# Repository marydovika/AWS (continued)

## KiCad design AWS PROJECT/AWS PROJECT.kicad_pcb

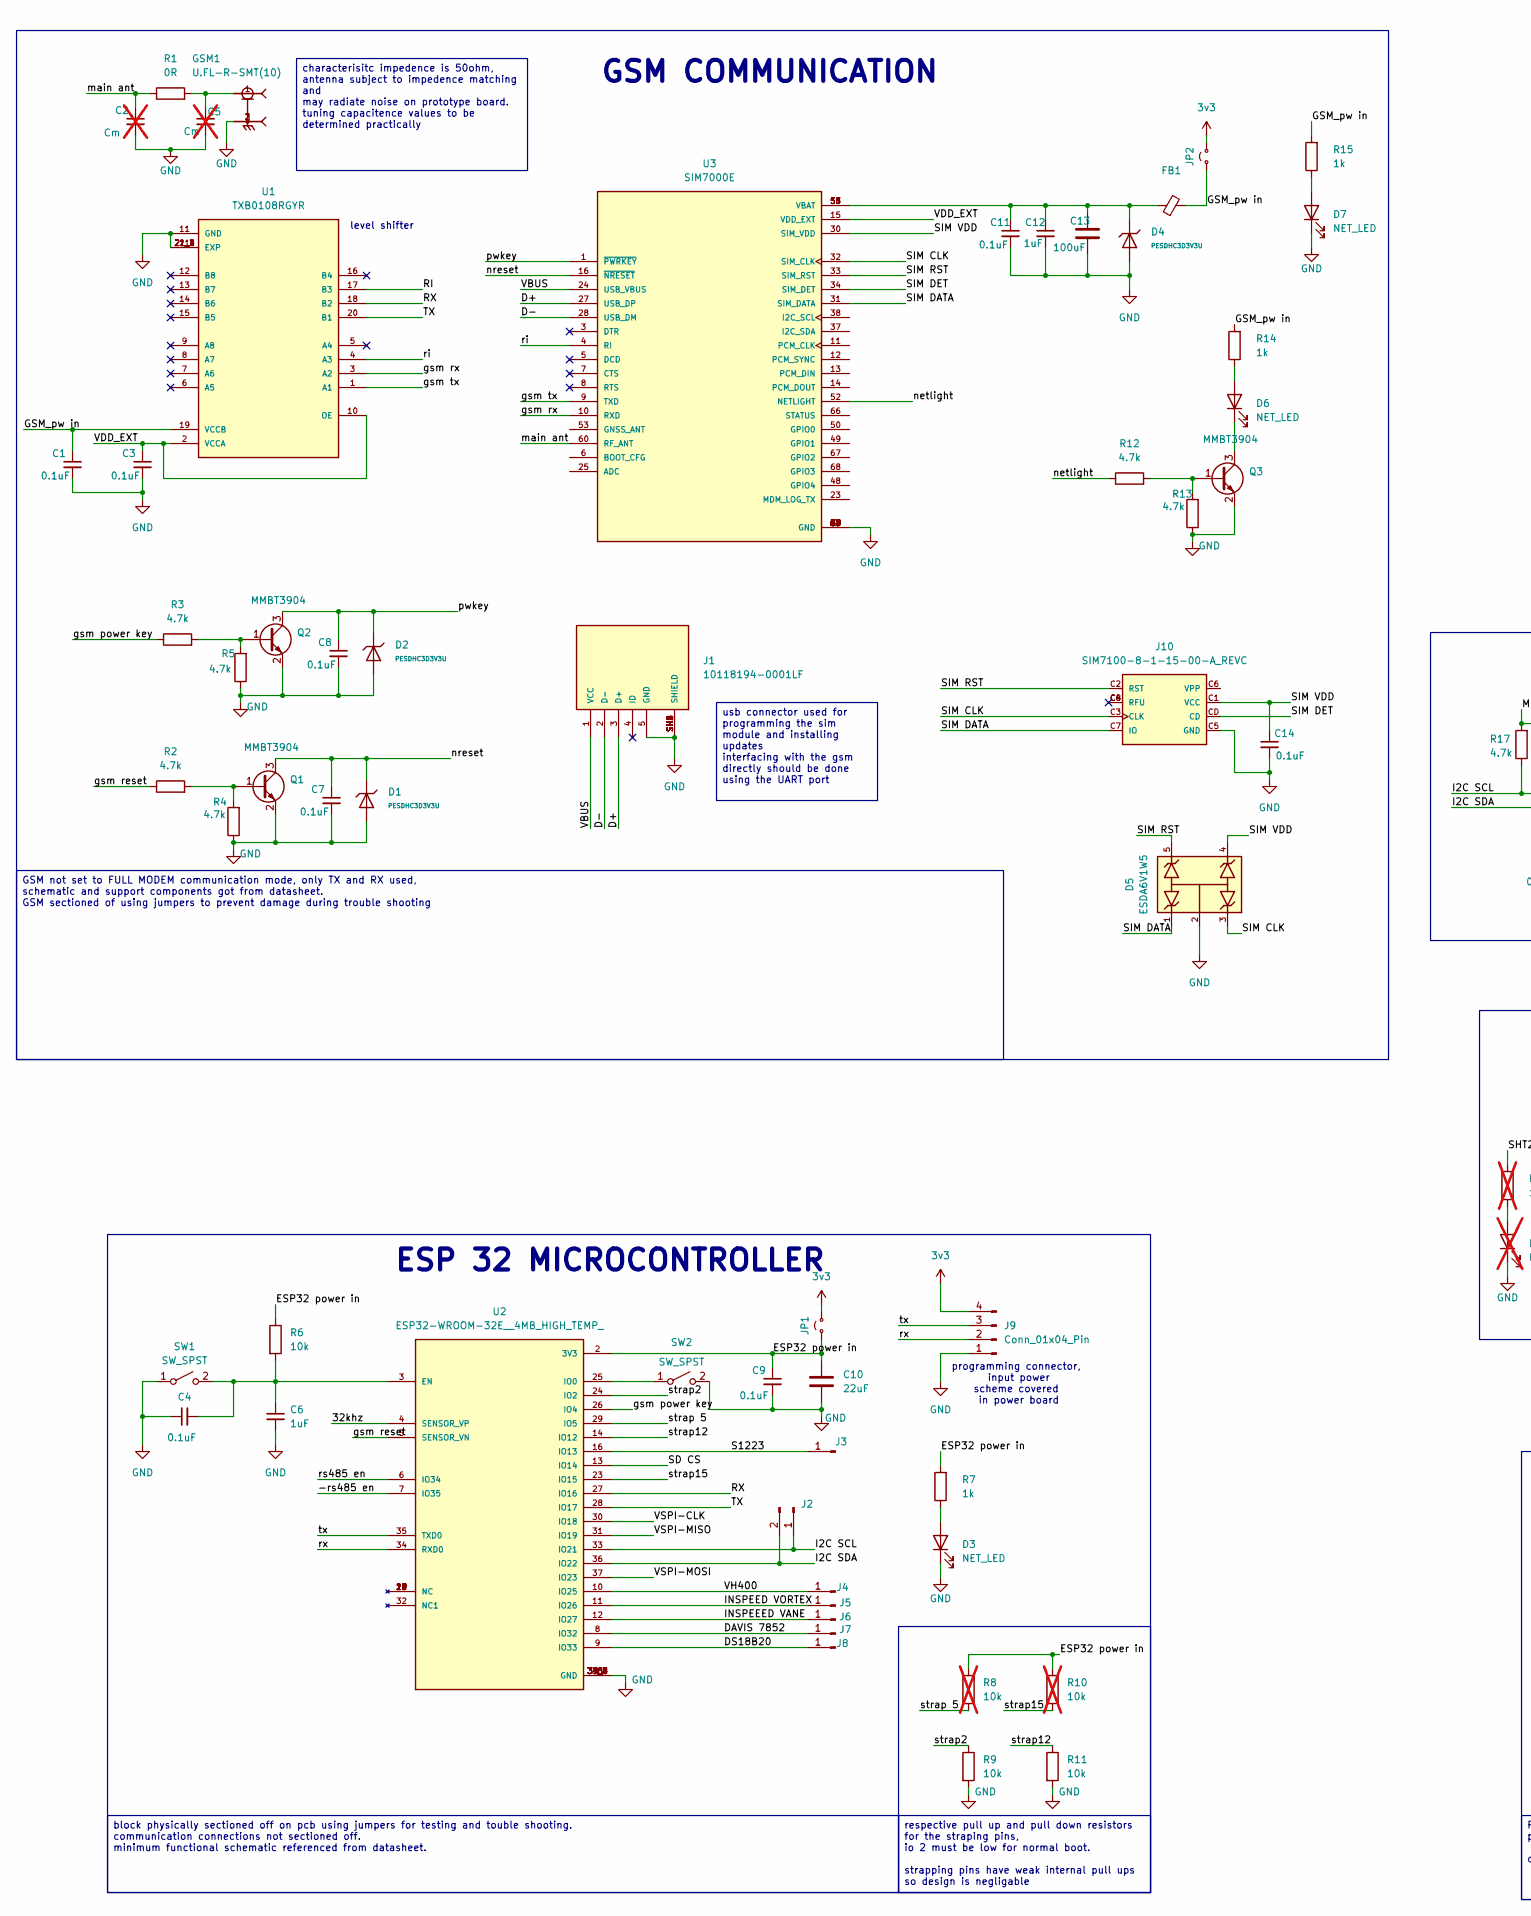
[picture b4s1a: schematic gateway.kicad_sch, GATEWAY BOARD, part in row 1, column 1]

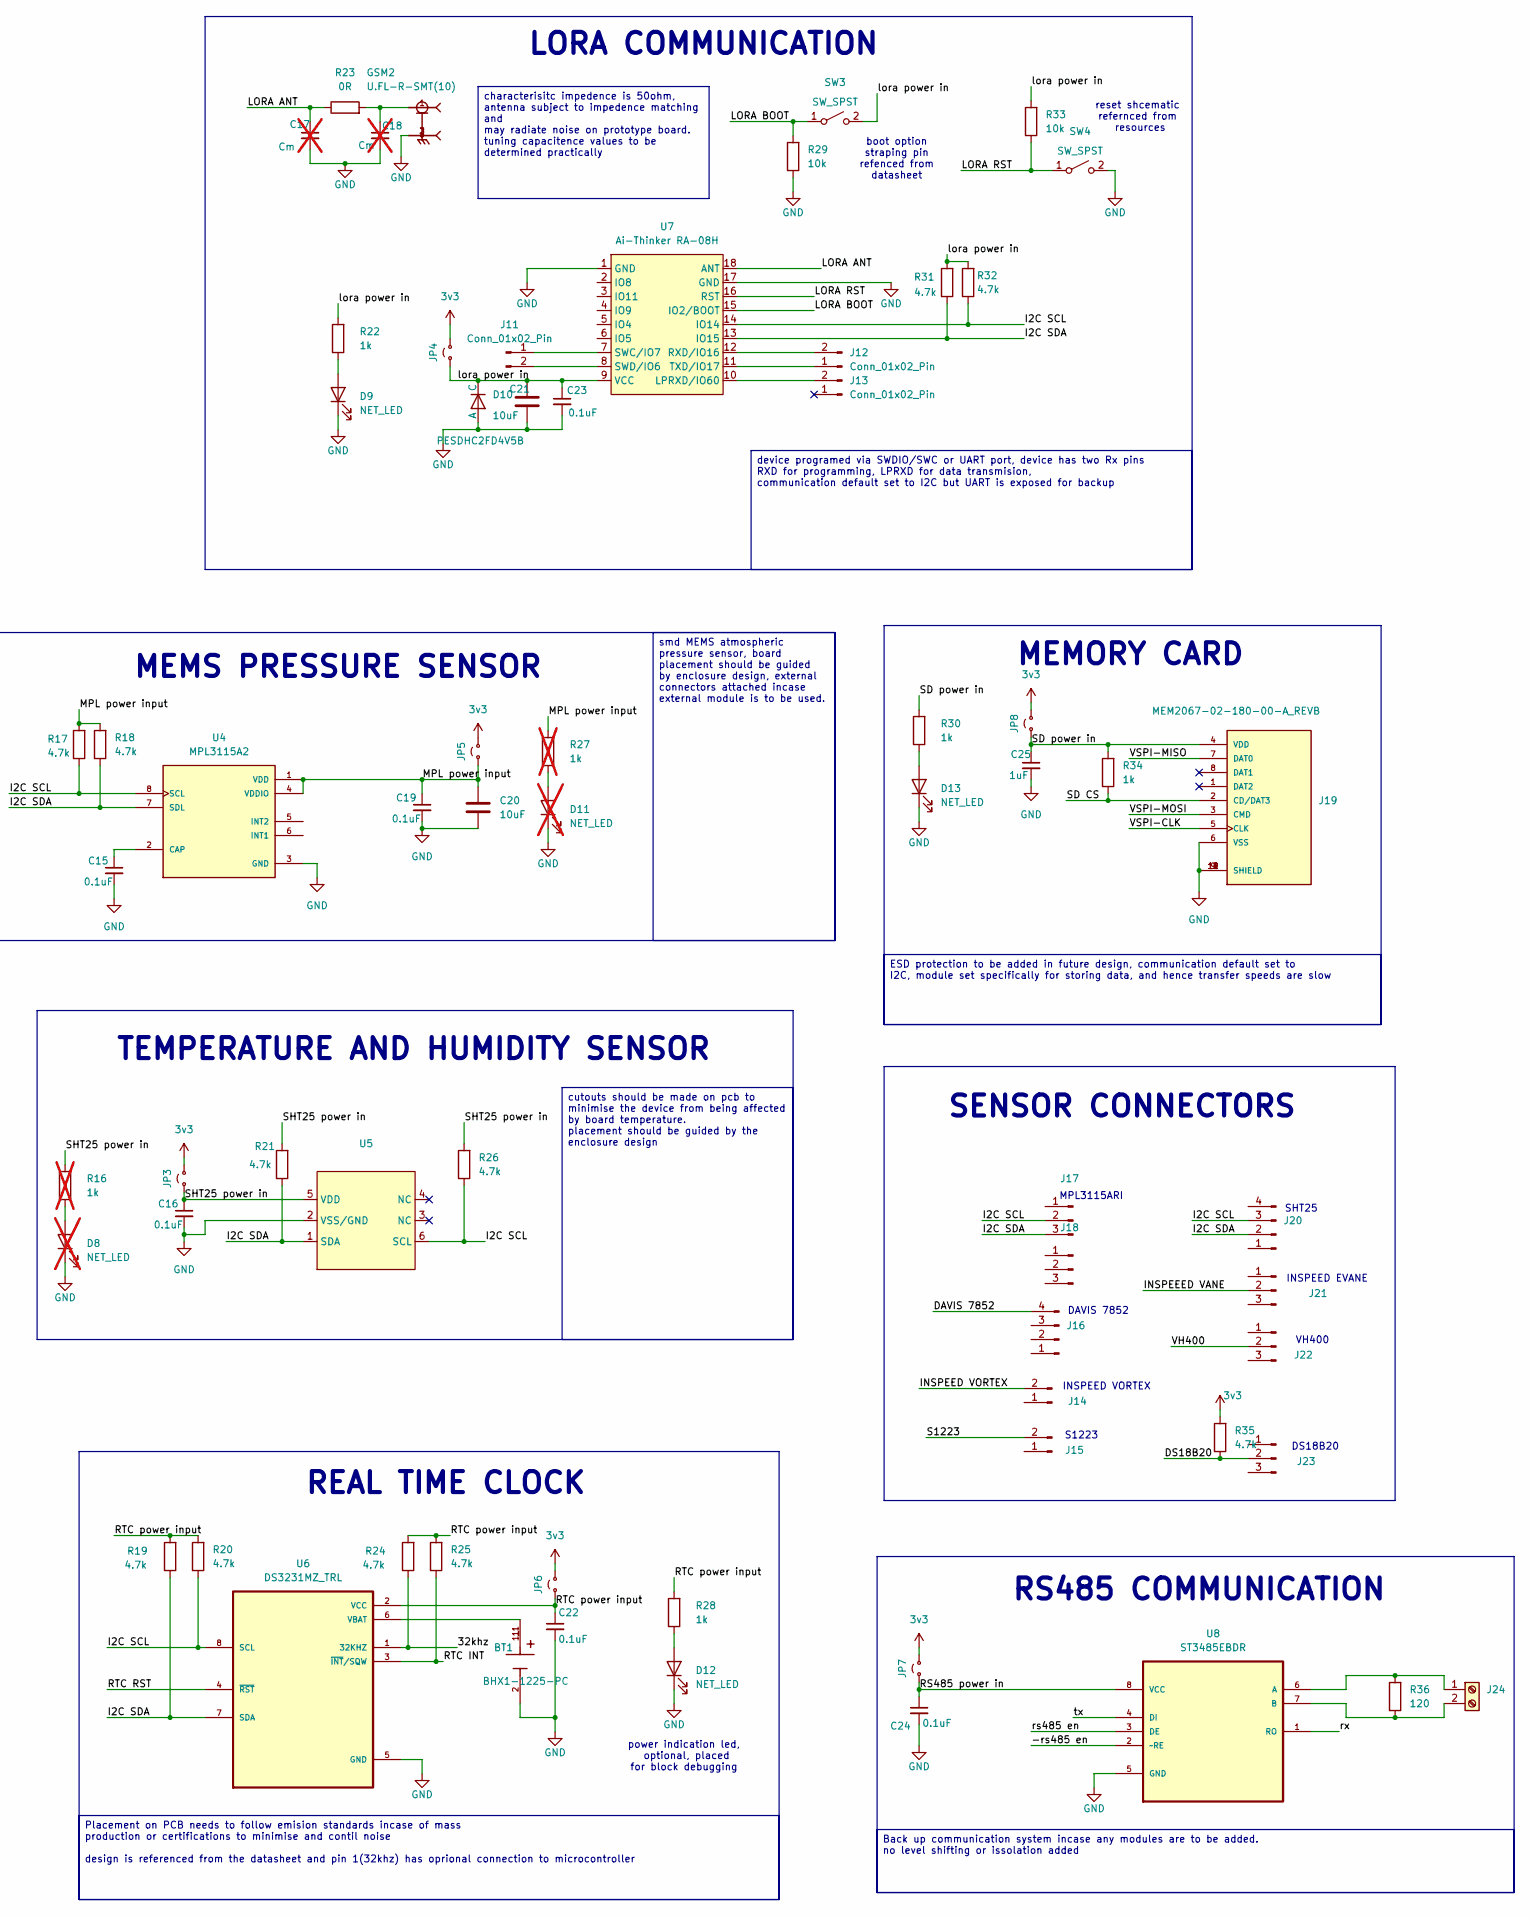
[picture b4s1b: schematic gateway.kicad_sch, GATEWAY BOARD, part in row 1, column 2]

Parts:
BT1: BHX1-1225-PC; BAT_BHX1-1225-PC; PARTREV H
C1, C3, C4, C7, C8, C9, C11, C14, C15, C16, C19, C22, C23, C24: 0.1uF; C_0603_1608Metric
C2, C5, C17, C18: Cm; C_0603_1608Metric; not fitted
C6, C12, C25: 1uF; C_0603_1608Metric
C10: 22uF; C_1206_3216Metric_Pad1.33x1.80mm_HandSolder
C13: 100uF; C_1206_3216Metric_Pad1.33x1.80mm_HandSolder
C20, C21: 10uF; C_1206_3216Metric_Pad1.33x1.80mm_HandSolder
D1, D2, D4: PESDHC3D3V3U; D_SOD-323F; Breakdown Voltage 12.3V; Part SMAJ10A; LCSC C41376407
D3, D6, D7, D9, D12, D13: NET_LED; D_0603_1608Metric
D5: ESDA6V1W5; SOT65P210X110-5N; PARTREV 2
D8, D11: NET_LED; D_0603_1608Metric; not fitted
D10: PESDHC2FD4V5B; Diodes_DFN1006-3
FB1: FerriteBead_Small; BEADC0603X33N
GSM1, GSM2: U.FL-R-SMT(10); U.FL_Molex_MCRF_73412-0110_Vertical; LCSC Part # C88373
J1: 10118194-0001LF; AMPHENOL_10118194-0001LF; PARTREV D
J2, J11, J12, J13: Conn_01x02_Pin; PinHeader_1x02_P1.00mm_Vertical
J3, J4, J5, J6, J7, J8: Conn_01x01_Pin; PinHeader_1x01_P1.00mm_Vertical
J9: Conn_01x04_Pin; PinHeader_1x04_P1.00mm_Vertical
J10: SIM7100-8-1-15-00-A_REVC; GCT_SIM7100-8-1-15-00-A_REVC; PARTREV C
J14, J15: Conn_01x02_Pin; PhoenixContact_MC_1,5_2-GF-3.5_1x02_P3.50mm_Horizontal_Thre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
J16, J20: Conn_01x04_Pin; PhoenixContact_MC_1,5_4-GF-3.5_1x04_P3.50mm_Horizontal_Thre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
J17, J18, J21, J22, J23: Conn_01x03_Pin; PhoenixContact_MC_1,5_3-GF-3.81_1x03_P3.81mm_Horizontal_Thr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
J19: MEM2067-02-180-00-A_REVB; GCT_MEM2067-02-180-00-A_REVB
J24: Screw_Terminal_01x02; PhoenixContact_MC_1,5_2-GF-3.5_1x02_P3.50mm_Horizontal_Thre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
JP1, JP2, JP3, JP4, JP5, JP6, JP7, JP8: Jumper_2_Small_Open; SolderJumper-2_P1.3mm_Open_RoundedPad1.0x1.5mm
Q1, Q2, Q3: MMBT3904; SOT-23
R1, R23: 0R; R_0603_1608Metric
R2, R3, R4, R5, R12, R13, R17, R18, R19, R20, R21, R24, R25, R26, R31, R32, R35: 4.7k; R_0603_1608Metric
R6, R9, R11, R29, R33: 10k; R_0603_1608Metric
R7, R14, R15, R22, R28, R30, R34: 1k; R_0603_1608Metric
R8, R10: 10k; R_0603_1608Metric; not fitted
R16, R27: 1k; R_0603_1608Metric; not fitted
R36: 120; R_0603_1608Metric
SW1, SW2, SW3, SW4: SW_SPST; SW_PUSH_6mm
U1: TXB0108RGYR; IC_TXB0108RGYR; PARTREV H
U2: ESP32-WROOM-32E__4MB_HIGH_TEMP_; XCVR_ESP32-WROOM-32E__4MB_HIGH_TEMP_; PARTREV 1.3
U3: SIM7000E; SIMCON_SIM7000E; PARTREV 1.01
U4: MPL3115A2; PSON125P300X500X120-8N
U5: DFN-6-1EP_3x3mm_P1mm_EP1.5x2.4mm
U6: DS3231MZ_TRL; SOIC127P600X175-8N
U7: Ai-Thinker RA-08H; RA-08H
U8: ST3485EBDR; SOIC127P600X175-8N; MPN ST3485EBDR

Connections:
3v3: J9.4, JP1.2 (B), JP2.2 (B), JP3.2 (B), JP4.2 (B), JP5.2 (B), JP6.2 (B), JP7.2 (B), JP8.2 (B), R35.2
/gate way/32khz: R24.1, U2.4 (SENSOR_VP), U6.1 (32KHZ)
/gate way/-rs485 en: U2.7 (IO35), U8.2 (~RE)
/gate way/D+: J1.3 (D+), U3.27 (USB_DP)
/gate way/D-: J1.2 (D-), U3.28 (USB_DM)
/gate way/DAVIS 7852: J7.1, J16.4, U2.8 (IO32)
/gate way/DS18B20: J8.1, J23.2, R35.1, U2.9 (IO33)
/gate way/ESP32 power in: C9.1, C10.1, JP1.1 (A), R6.1, R7.2, R8.1, R10.1, U2.2 (3V3)
/gate way/GSM_pw in: C1.1, FB1.2, JP2.1 (A), R14.2, R15.2, U1.19 (VCCB)
/gate way/I2C SCL: J2.1, J17.2, J20.3, R17.1, R20.1, R26.1, R32.1, U2.33 (IO21), U4.8 (SCL), U5.6 (SCL), U6.8 (SCL), U7.14 (IO14)
/gate way/I2C SDA: J2.2, J17.3, J20.2, R18.1, R19.1, R21.1, R31.1, U2.36 (IO22), U4.7 (SDL), U5.1 (SDA), U6.7 (SDA), U7.13 (IO15)
/gate way/INSPEED VORTEX: J5.1, J14.2, U2.11 (IO26)
/gate way/INSPEEED VANE: J6.1, J21.2, U2.12 (IO27)
/gate way/LORA ANT: C17.1, R23.1, U7.18 (ANT)
/gate way/LORA BOOT: R29.2, SW3.1 (A), U7.15 (IO2/BOOT)
/gate way/LORA RST: R33.1, SW4.1 (A), U7.16 (RST)
/gate way/MPL power input: C19.1, C20.1, JP5.1 (A), R17.2, R18.2, R27.2, U4.1 (VDD), U4.4 (VDDIO)
/gate way/RI: U1.17 (B3)
/gate way/RS485 power in: C24.1, JP7.1 (A), U8.8 (VCC)
/gate way/RTC INT: R25.1, U6.3 (~INT/SQW)
/gate way/RTC RST: U6.4 (~RST)
/gate way/RTC power input: C22.1, JP6.1 (A), R19.2, R20.2, R24.2, R25.2, R28.2, U6.2 (VCC)
/gate way/RX: U1.18 (B2), U2.27 (IO16)
/gate way/S1223: J3.1, J15.2, U2.16 (IO13)
/gate way/SD CS: J19.2 (CD/DAT3), R34.1, U2.13 (IO14)
/gate way/SD power in: C25.1, J19.4 (VDD), JP8.1 (A), R30.2, R34.2
/gate way/SHT25 power in: C16.1, JP3.1 (A), R16.2, R21.2, R26.2, U5.5 (VDD)
/gate way/SIM CLK: D5.3, J10.C3 (CLK), U3.32 (SIM_CLK)
/gate way/SIM DATA: D5.1, J10.C7 (IO), U3.31 (SIM_DATA)
/gate way/SIM DET: J10.CD, U3.34 (SIM_DET)
/gate way/SIM RST: D5.5, J10.C2 (RST), U3.33 (SIM_RST)
/gate way/SIM VDD: C14.1, D5.4, J10.C1 (VCC), U3.30 (SIM_VDD)
/gate way/TX: U1.20 (B1), U2.28 (IO17)
/gate way/VBUS: J1.1 (VCC), U3.24 (USB_VBUS)
/gate way/VDD_EXT: C3.1, U1.2 (VCCA), U1.10 (OE), U3.15 (VDD_EXT)
/gate way/VH400: J4.1, J22.2, U2.10 (IO25)
/gate way/VSPI-CLK: J19.5 (CLK), U2.30 (IO18)
/gate way/VSPI-MISO: J19.7 (DAT0), U2.31 (IO19)
/gate way/VSPI-MOSI: J19.3 (CMD), U2.37 (IO23)
/gate way/gsm power key: R3.1, U2.26 (IO4)
/gate way/gsm reset: R2.1, U2.5 (SENSOR_VN)
/gate way/gsm rx: U1.3 (A2), U3.10 (RXD)
/gate way/gsm tx: U1.1 (A1), U3.9 (TXD)
/gate way/lora power in: C21.1, C23.1, D10.2 (C), JP4.1 (A), R22.2, R31.2, R32.2, R33.2, SW3.2 (B), U7.9 (VCC)
/gate way/main ant: C2.1, R1.1, U3.60 (RF_ANT)
/gate way/netlight: R12.1, U3.52 (NETLIGHT)
/gate way/nreset: C7.1, D1.1, Q1.3 (C), U3.16 (~NRESET)
/gate way/pwkey: C8.1, D2.1, Q2.3 (C), U3.1 (~PWRKEY)
/gate way/ri: U1.4 (A3), U3.4 (RI)
/gate way/rs485 en: U2.6 (IO34), U8.3 (DE)
/gate way/rx: J9.2, U2.34 (RXD0), U8.1 (RO)
/gate way/strap2: R9.1, U2.24 (IO2)
/gate way/strap12: R11.1, U2.14 (IO12)
/gate way/strap15: R10.2, U2.23 (IO15)
/gate way/strap 5: R8.2, U2.29 (IO5)
/gate way/tx: J9.3, U2.35 (TXD0), U8.4 (DI)
GND: BT1.2, C1.2, C2.2, C3.2, C4.1, C5.2, C6.2, C7.2, C8.2, C9.2, C10.2, C11.2, C12.2, C13.2, C14.2, C15.2, C16.2, C17.2, C18.2, C19.2, C20.2, C21.2, C22.2, C23.2, C24.2, C25.2, D1.2, D2.2, D3.1 (K), D4.2, D5.2, D7.1 (K), D8.1 (K), D9.1 (K), D10.1 (A), D11.1 (K), D12.1 (K), D13.1 (K), GSM1.2, GSM1.3, GSM2.2, GSM2.3, J1.5 (GND), J1.SH1 (SHIELD), J1.SH2 (SHIELD), J1.SH3 (SHIELD), J1.SH4 (SHIELD), J1.SH5 (SHIELD), J1.SH6 (SHIELD), J9.1, J10.C5 (GND), J19.6 (VSS), J19.9 (SHIELD), J19.10 (SHIELD), J19.11 (SHIELD), J19.12 (SHIELD), Q1.2 (E), Q2.2 (E), Q3.2 (E), R4.1, R5.1, R9.2, R11.2, R13.1, R29.1, SW1.1 (A), SW2.2 (B), SW4.2 (B), U1.11 (GND), U1.21 (EXP), U1.21_1 (EXP), U1.21_2 (EXP), U1.21_3 (EXP), U1.21_4 (EXP), U2.1 (GND), U2.15 (GND), U2.38 (GND), U2.39_1 (GND), U2.39_2 (GND), U2.39_3 (GND), U2.39_4 (GND), U2.39_5 (GND), U2.39_6 (GND), U2.39_7 (GND), U2.39_8 (GND), U2.39_9 (GND), U3.2 (GND), U3.17 (GND), U3.18 (GND), U3.29 (GND), U3.39 (GND), U3.45 (GND), U3.46 (GND), U3.54 (GND), U3.58 (GND), U3.59 (GND), U3.61 (GND), U3.62 (GND), U3.63 (GND), U3.64 (GND), U3.65 (GND), U4.3 (GND), U5.2 (VSS/GND), U6.5 (GND), U7.1 (GND), U7.17 (GND), U8.5 (GND)
unnamed: C5.1, GSM1.1, R1.2
unnamed: C11.1, C12.1, C13.1, D4.1, FB1.1, U3.55 (VBAT), U3.56 (VBAT), U3.57 (VBAT)
unnamed: C18.1, GSM2.1, R23.2
unnamed: D3.2 (A), R7.1
unnamed: D6.2 (A), R14.1
unnamed: D6.1 (K), Q3.3 (C)
unnamed: D7.2 (A), R15.1
unnamed: D8.2 (A), R16.1
unnamed: D9.2 (A), R22.1
unnamed: D11.2 (A), R27.1
unnamed: D12.2 (A), R28.1
unnamed: D13.2 (A), R30.1
unnamed: J11.1, U7.7 (SWC/IO7)
unnamed: J11.2, U7.8 (SWD/IO6)
unnamed: J12.1, U7.11 (TXD/IO17)
unnamed: J12.2, U7.12 (RXD/IO16)
unnamed: J13.2, U7.10 (LPRXD/IO60)
unnamed: J24.1, R36.2, U8.6 (A)
unnamed: J24.2, R36.1, U8.7 (B)
unnamed: Q1.1 (B), R2.2, R4.2
unnamed: Q2.1 (B), R3.2, R5.2
unnamed: Q3.1 (B), R12.2, R13.2
unnamed: C4.2, C6.1, R6.2, SW1.2 (B), U2.3 (EN)
unnamed: SW2.1 (A), U2.25 (IO0)
unnamed: C15.1, U4.2 (CAP)
unnamed: BT1.1, BT1.1_1, U6.6 (VBAT)

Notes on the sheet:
REAL TIME CLOCK
MPL3115ARI
power indication led, optional, placed for block debugging
DS18B20
programming connector, input power scheme covered in power board
S1223
MEMORY CARD
MEMS PRESSURE SENSOR
INSPEED VORTEX
SENSOR CONNECTORS
level shifter
DAVIS 7852
SHT25
LORA COMMUNICATION
RS485 COMMUNICATION
TEMPERATURE AND HUMIDITY SENSOR
GSM COMMUNICATION
boot option straping pin refenced from datasheet
ESP 32 MICROCONTROLLER
reset shcematic refernced from resources
VH400
INSPEED EVANE
ESD protection to be added in future design, communication default set to I2C, module set specifically for storing data, and hence transfer speeds are slow
GSM not set to FULL MODEM communication mode, only TX and RX used, schematic and support components got from datasheet. GSM sectioned of using jumpers to prevent damage during trouble shooting
Placement on PCB needs to follow emision standards incase of mass production or certifications to minimise and contil noise design is referenced from the datasheet and pin 1(32khz) has oprional connection to microcontroller
device programed via SWDIO/SWC or UART port, device has two Rx pins RXD for programming, LPRXD for data transmision, communication default set to I2C but UART is exposed for backup
characterisitc impedence is 50ohm, antenna subject to impedence matching and may radiate noise on prototype board. tuning capacitence values to be determined practically
block physically sectioned off on pcb using jumpers for testing and touble shooting. communication connections not sectioned off. minimum functional schematic referenced from datasheet.
respective pull up and pull down resistors for the straping pins, io 2 must be low for normal boot. strapping pins have weak internal pull ups so design is negligable
usb connector used for programming the sim module and installing updates interfacing with the gsm directly should be done using the UART port
smd MEMS atmospheric pressure sensor, board placement should be guided by enclosure design, external connectors attached incase external module is to be used.
Back up communication system incase any modules are to be added. no level shifting or issolation added
cutouts should be made on pcb to minimise the device from being affected by board temperature. placement should be guided by the enclosure design

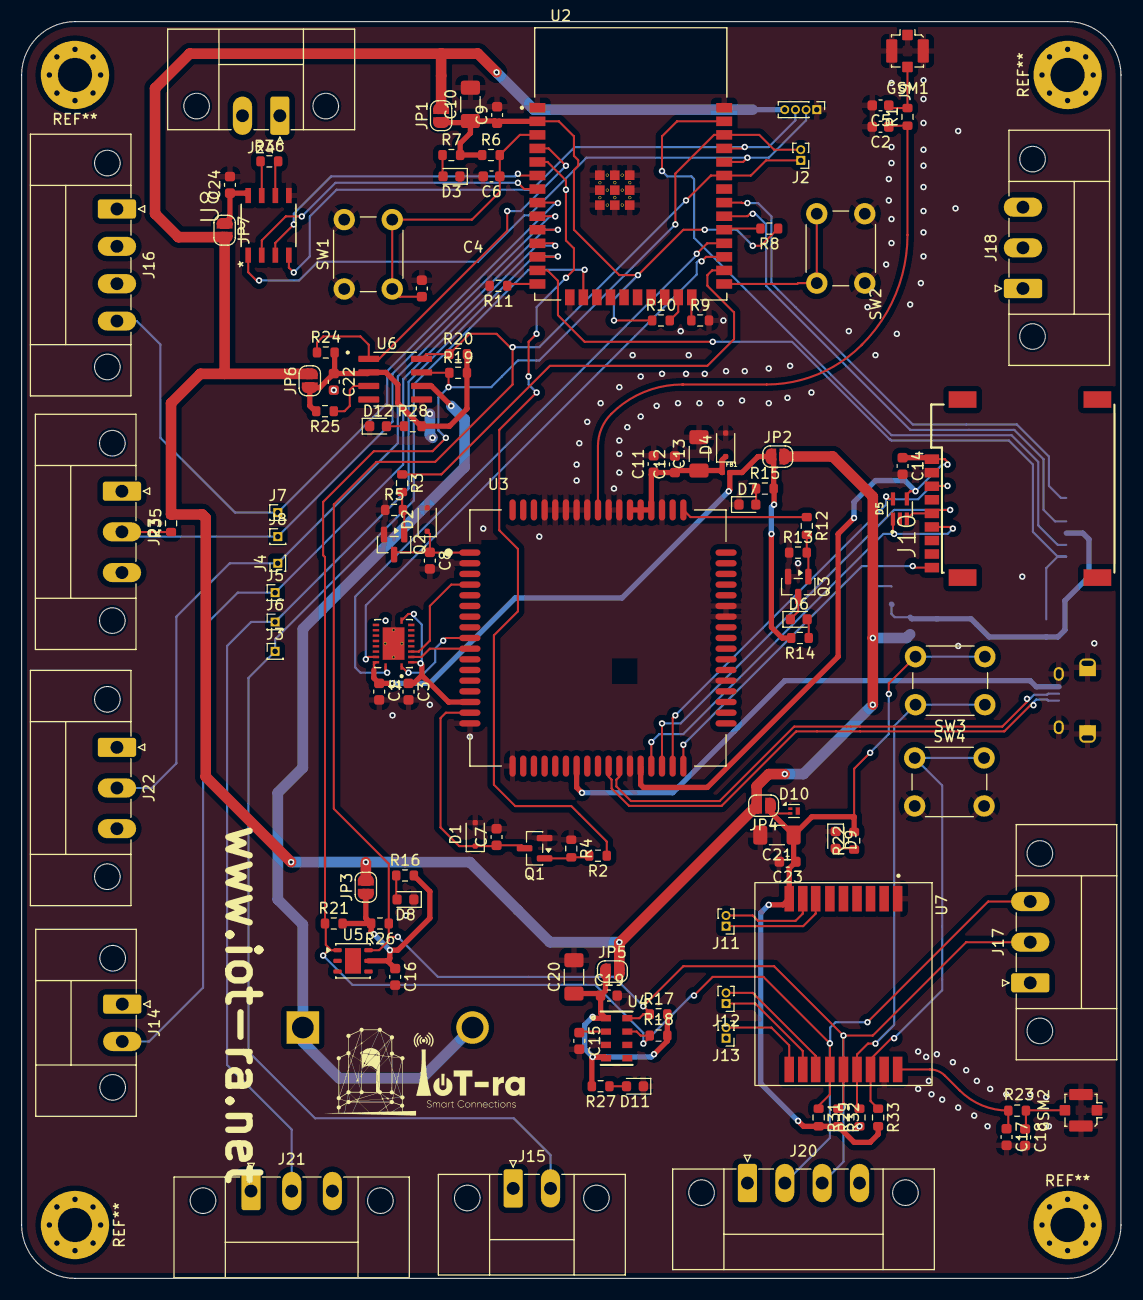
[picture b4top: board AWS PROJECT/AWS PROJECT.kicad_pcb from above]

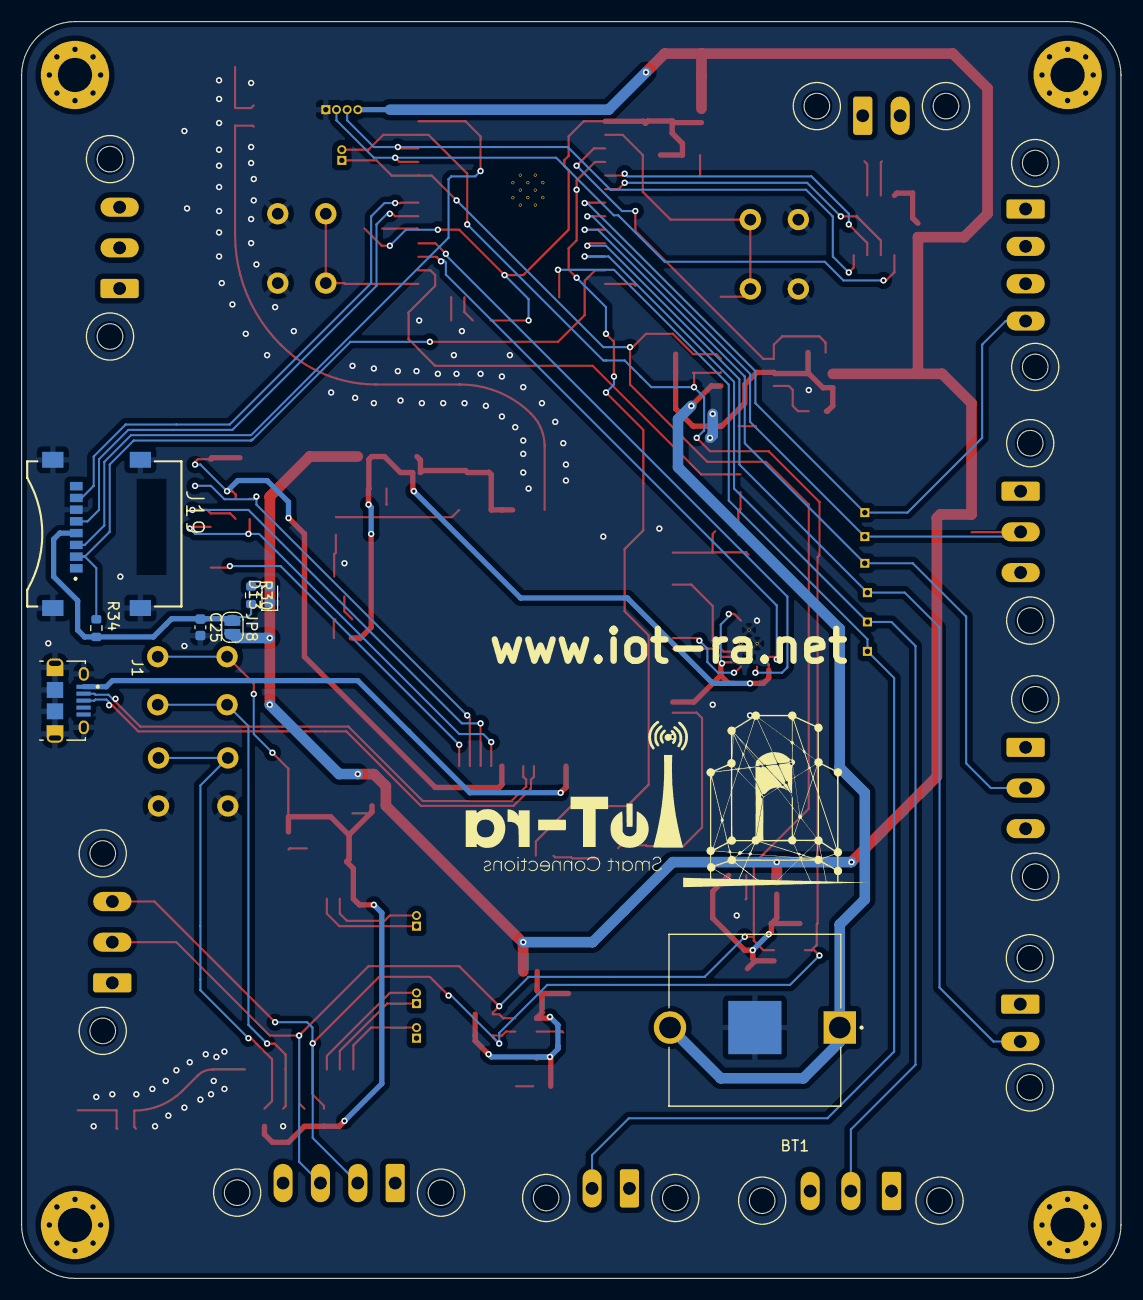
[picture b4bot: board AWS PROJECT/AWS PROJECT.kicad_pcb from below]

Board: 2 copper layers, 103.0 x 117.8 mm, 125 parts (8 on the bottom side), 81 nets.

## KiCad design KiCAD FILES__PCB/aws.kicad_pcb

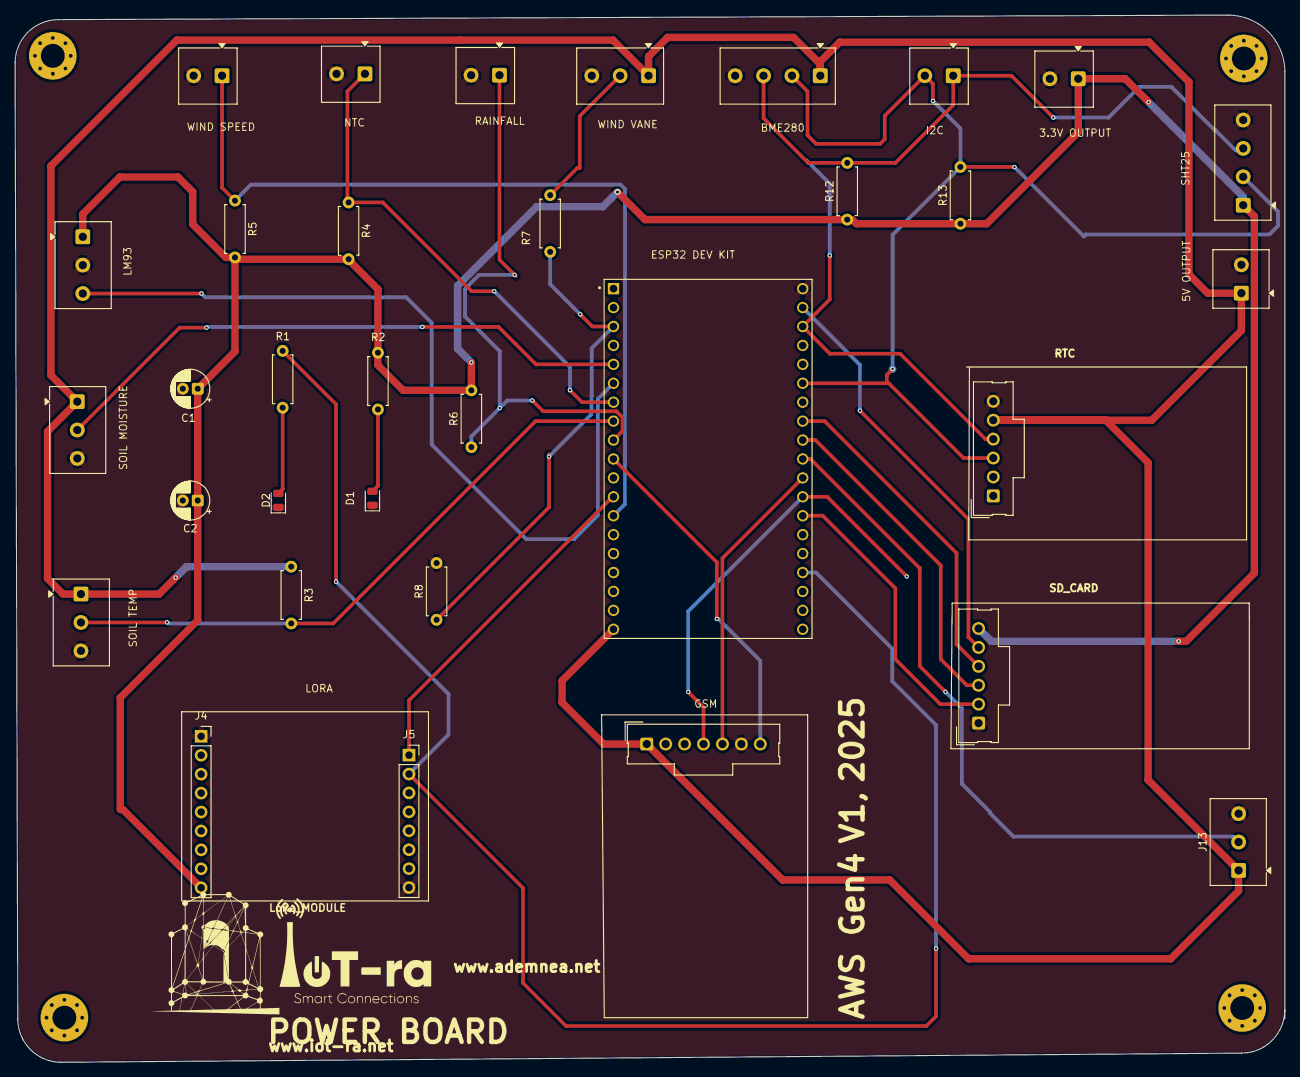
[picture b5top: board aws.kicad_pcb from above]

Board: 2 copper layers, 170.4 x 140.6 mm, 33 parts (0 on the bottom side), 25 nets.

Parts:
C1: 10uF; CP_Radial_D5.0mm_P2.00mm
C2: 0.1uF; CP_Radial_D5.0mm_P2.00mm
D1, D2: LED; LED_0805_2012Metric
J1: Real Time Clock; Molex_SL_171971-0006_1x06_P2.54mm_Vertical
J2: GSM; Molex_SL_171971-0007_1x07_P2.54mm_Vertical
J3: 5V; TerminalBlock_Phoenix_MKDS-1-2-3.81_1x02_P3.81mm_Horizontal
J4: Conn_01x09_Socket; PinSocket_1x09_P2.54mm_Vertical
J5: Conn_01x08_Socket; PinSocket_1x08_P2.54mm_Vertical
J6: I2C; TerminalBlock_Phoenix_MKDS-1-2-3.81_1x02_P3.81mm_Horizontal
J7: WIND SPEED; TerminalBlock_Phoenix_MKDS-1-2-3.81_1x02_P3.81mm_Horizontal
J8: LM93; TerminalBlock_Phoenix_MKDS-1-3-3.81_1x03_P3.81mm_Horizontal
J9: RAINFALL SENSOR; TerminalBlock_Phoenix_MKDS-1-2-3.81_1x02_P3.81mm_Horizontal
J10: WIND VANE; TerminalBlock_Phoenix_MKDS-1-3-3.81_1x03_P3.81mm_Horizontal
J11: SD CARD; Molex_SL_171971-0006_1x06_P2.54mm_Vertical
J11#2: SOIL MOISTURE; TerminalBlock_Phoenix_MKDS-1-3-3.81_1x03_P3.81mm_Horizontal
J12: SOIL TEMP; TerminalBlock_Phoenix_MKDS-1-3-3.81_1x03_P3.81mm_Horizontal
J13: DHT 22; TerminalBlock_Phoenix_MKDS-1-3-3.81_1x03_P3.81mm_Horizontal
J14: SHT25; TerminalBlock_Phoenix_MKDS-1-4-3.81_1x04_P3.81mm_Horizontal
J15: NTC THERMISTOR; TerminalBlock_Phoenix_MKDS-1-2-3.81_1x02_P3.81mm_Horizontal
J17: BME280; TerminalBlock_Phoenix_MKDS-1-4-3.81_1x04_P3.81mm_Horizontal
J18: 3.3V; TerminalBlock_Phoenix_MKDS-1-2-3.81_1x02_P3.81mm_Horizontal
R1, R7: 1k; R_Axial_DIN0207_L6.3mm_D2.5mm_P7.62mm_Horizontal
R2: 0.47k; R_Axial_DIN0207_L6.3mm_D2.5mm_P7.62mm_Horizontal
R3, R4, R5, R6, R12, R13: 4.7k; R_Axial_DIN0207_L6.3mm_D2.5mm_P7.62mm_Horizontal
R8: 2k; R_Axial_DIN0207_L6.3mm_D2.5mm_P7.62mm_Horizontal
U1: ESP32-DEVKITC-32U; MODULE_ESP32-DEVKITC-32U

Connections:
+3.3V: C1.1, C2.1, J4.9, J8.1, J11.6, J14.1, J18.1, R2.1, R4.2, R5.2, R6.2, R12.1, R13.1
+5V: J1.5, J2.1, J3.1, J10.1, J11#2.1, J12.1, J13.1, J17.1, R3.1, U1.19 (EXT_5V)
G4: J11.2, U1.26 (IO4)
G5: J13.2, U1.29 (IO5)
G12: J7.1, R5.1, U1.13 (IO12)
G14: J5.1, U1.12 (IO14)
G15: J5.2, R1.1, U1.23 (IO15)
G16: J2.4, U1.27 (IO16)
G17: J2.5, U1.28 (IO17)
G18: J11.3, U1.30 (IO18)
G19: J11.4, U1.31 (IO19)
G21: J1.3, J6.2, J14.2, J17.2, R13.2, U1.33 (IO21)
G22: J1.4, J6.1, J14.3, J17.3, R12.2, U1.36 (IO22)
G23: J11.5, U1.37 (IO23)
G25: J9.1, R6.1, U1.9 (IO25)
G32: J15.1, R4.1, U1.7 (IO32)
G33: J12.2, R3.2, U1.8 (IO33)
G34: J11#2.2, U1.5 (IO34)
G35: J8.3, U1.6 (IO35)
G36: R7.2, R8.1, U1.3 (SENSOR_VP)
GND: C1.2, C2.2, D1.1 (K), D2.1 (K), J1.6, J2.6, J3.2, J4.1, J5.8, J7.2, J8.2, J9.2, J10.3, J11.1, J11#2.3, J12.3, J13.3, J14.4, J15.2, J17.4, J18.2, R8.2, U1.38 (GND3)
GSM_RST: J2.7, U1.10 (IO26)
unnamed: D1.2 (A), R2.2
unnamed: D2.2 (A), R1.2
unnamed: J10.2, R7.1
